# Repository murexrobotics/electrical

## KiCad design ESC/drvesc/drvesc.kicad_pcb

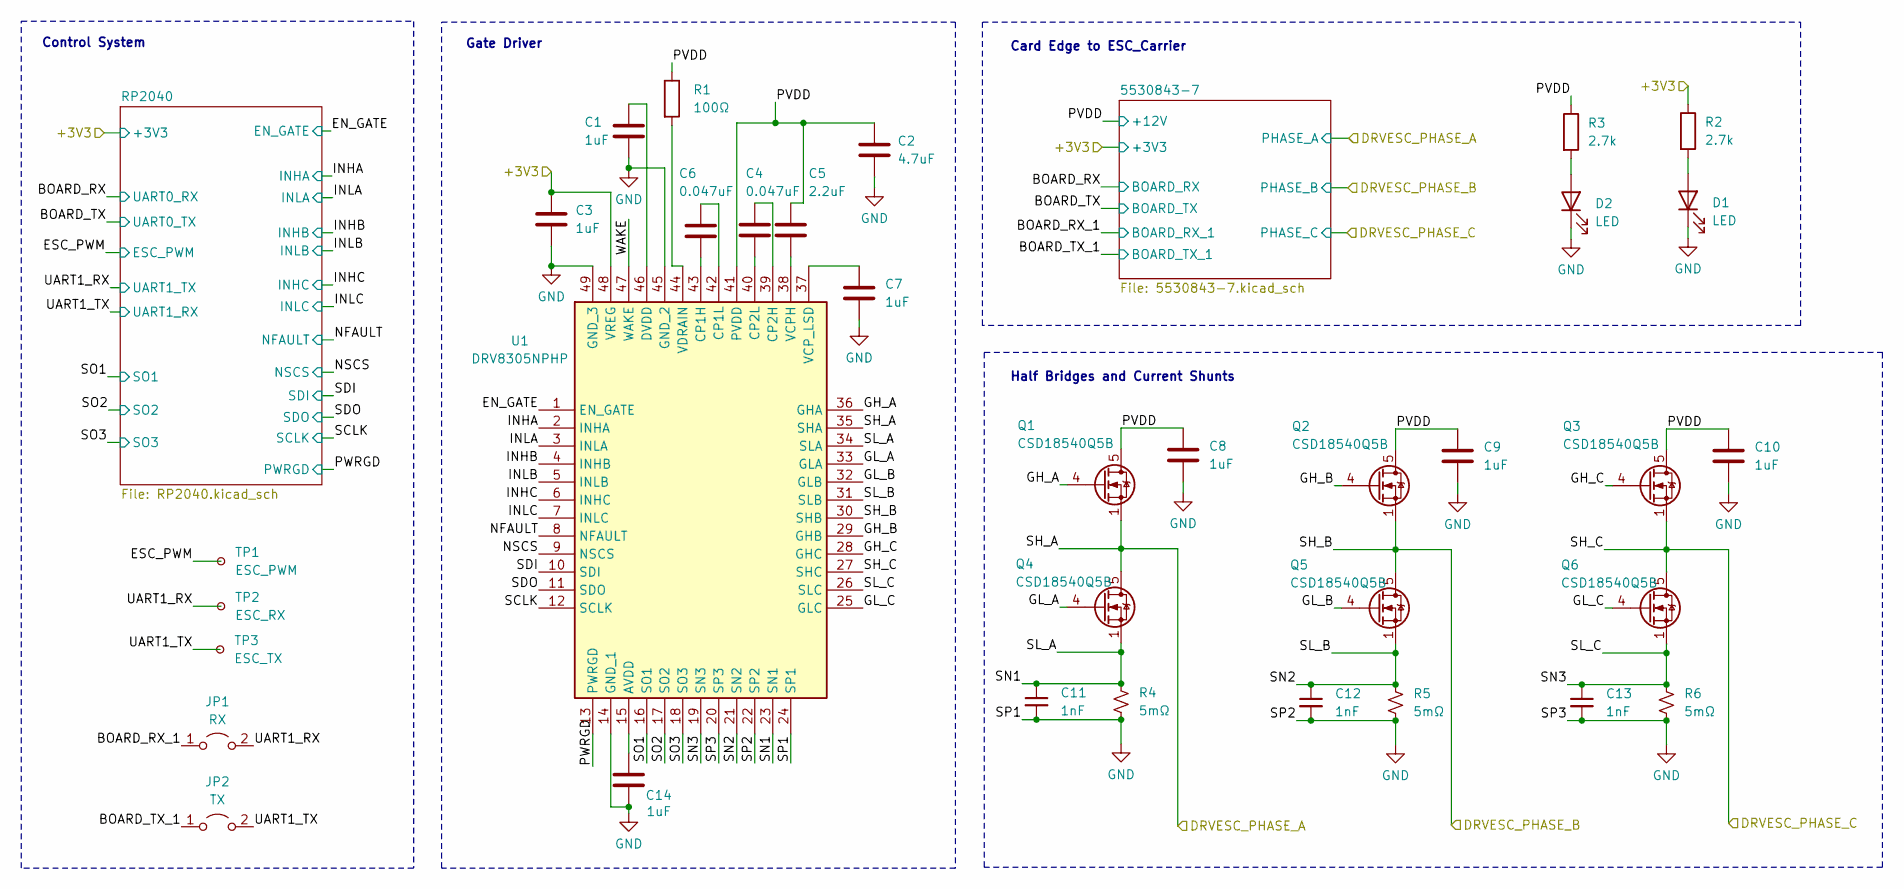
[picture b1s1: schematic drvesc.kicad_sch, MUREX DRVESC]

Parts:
C1, C3, C7, C8, C9, C10, C14: 1uF; C_0603_1608Metric
C2: 4.7uF; C_0603_1608Metric
C4, C6: 0.047uF; C_0603_1608Metric
C5: 2.2uF; C_0603_1608Metric
C11, C12, C13: 1nF; C_0603_1608Metric
D1, D2: LED; LED_0603_1608Metric
JP1: RX; SolderJumper-2_P1.3mm_Open_RoundedPad1.0x1.5mm
JP2: TX; SolderJumper-2_P1.3mm_Open_RoundedPad1.0x1.5mm
Q1, Q2, Q3, Q4, Q5, Q6: CSD18540Q5B; TDSON-8-1
R1: 100Ω; R_0603_1608Metric
R2, R3: 2.7k; R_0603_1608Metric
R4, R5, R6: 5mΩ; R_2512_6332Metric
TP1: ESC_PWM; PinHeader_1x01_P2.54mm_Vertical
TP2: ESC_RX; PinHeader_1x01_P2.54mm_Vertical
TP3: ESC_TX; PinHeader_1x01_P2.54mm_Vertical
U1: DRV8305NPHP; QFP50P900X900X120-49N; Manufacturer_Part_Number DRV8305NPHP; Mouser Part Number 595-DRV8305NPHP

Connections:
/+3V3: C3.1, R2.1, U1.48 (VREG); also elsewhere on the board
/BOARD_RX_1: JP1.1 (A); also elsewhere on the board
/BOARD_TX_1: JP2.1 (A); also elsewhere on the board
/EN_GATE: U1.1 (EN_GATE); also elsewhere on the board
/ESC_PWM: TP1.1; also elsewhere on the board
/GH_A: Q1.4 (G), U1.36 (GHA)
/GH_B: Q2.4 (G), U1.29 (GHB)
/GH_C: Q3.4 (G), U1.28 (GHC)
/GL_A: Q4.4 (G), U1.33 (GLA)
/GL_B: Q5.4 (G), U1.32 (GLB)
/GL_C: Q6.4 (G), U1.25 (GLC)
/INHA: U1.2 (INHA); also elsewhere on the board
/INHB: U1.4 (INHB); also elsewhere on the board
/INHC: U1.6 (INHC); also elsewhere on the board
/INLA: U1.3 (INLA); also elsewhere on the board
/INLB: U1.5 (INLB); also elsewhere on the board
/INLC: U1.7 (INLC); also elsewhere on the board
/NFAULT: U1.8 (NFAULT); also elsewhere on the board
/NSCS: U1.9 (NSCS); also elsewhere on the board
/PVDD: C2.1, C5.1, C8.1, C9.1, C10.1, Q1.5 (D), Q2.5 (D), Q3.5 (D), R1.1, R3.1, U1.41 (PVDD); also elsewhere on the board
/PWRGD: U1.13 (PWRGD); also elsewhere on the board
/SCLK: U1.12 (SCLK); also elsewhere on the board
/SDI: U1.10 (SDI); also elsewhere on the board
/SDO: U1.11 (SDO); also elsewhere on the board
/SH_A: Q1.1 (S), Q1.2 (S), Q1.3 (S), Q4.5 (D), U1.35 (SHA); also elsewhere on the board
/SH_B: Q2.1 (S), Q2.2 (S), Q2.3 (S), Q5.5 (D), U1.30 (SHB); also elsewhere on the board
/SH_C: Q3.1 (S), Q3.2 (S), Q3.3 (S), Q6.5 (D), U1.27 (SHC); also elsewhere on the board
/SL_A: C11.1, Q4.1 (S), Q4.2 (S), Q4.3 (S), R4.1, U1.23 (SN1), U1.34 (SLA)
/SL_B: C12.1, Q5.1 (S), Q5.2 (S), Q5.3 (S), R5.1, U1.21 (SN2), U1.31 (SLB)
/SL_C: C13.1, Q6.1 (S), Q6.2 (S), Q6.3 (S), R6.1, U1.19 (SN3), U1.26 (SLC)
/SO1: U1.16 (SO1); also elsewhere on the board
/SO2: U1.17 (SO2); also elsewhere on the board
/SO3: U1.18 (SO3); also elsewhere on the board
/UART1_RX: JP1.2 (B), TP2.1; also elsewhere on the board
/UART1_TX: JP2.2 (B), TP3.1; also elsewhere on the board
/WAKE: U1.47 (WAKE)
GND: C1.2, C2.2, C3.2, C7.2, C8.2, C9.2, C10.2, C11.2, C12.2, C13.2, C14.2, D1.1 (K), D2.1 (K), R4.2, R5.2, R6.2, U1.14 (GND_1), U1.20 (SP3), U1.22 (SP2), U1.24 (SP1), U1.45 (GND_2), U1.49 (GND_3); also elsewhere on the board
unnamed: D1.2 (A), R2.2
unnamed: D2.2 (A), R3.2
unnamed: C14.1, U1.15 (AVDD)
unnamed: C6.2, U1.43 (CP1H)
unnamed: C6.1, U1.42 (CP1L)
unnamed: C4.1, U1.39 (CP2H)
unnamed: C4.2, U1.40 (CP2L)
unnamed: C1.1, U1.46 (DVDD)
unnamed: C5.2, U1.38 (VCPH)
unnamed: C7.1, U1.37 (VCP_LSD)
unnamed: R1.2, U1.44 (VDRAIN)

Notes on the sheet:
Half Bridges and Current Shunts
Gate Driver
Control System
Card Edge to ESC_Carrier

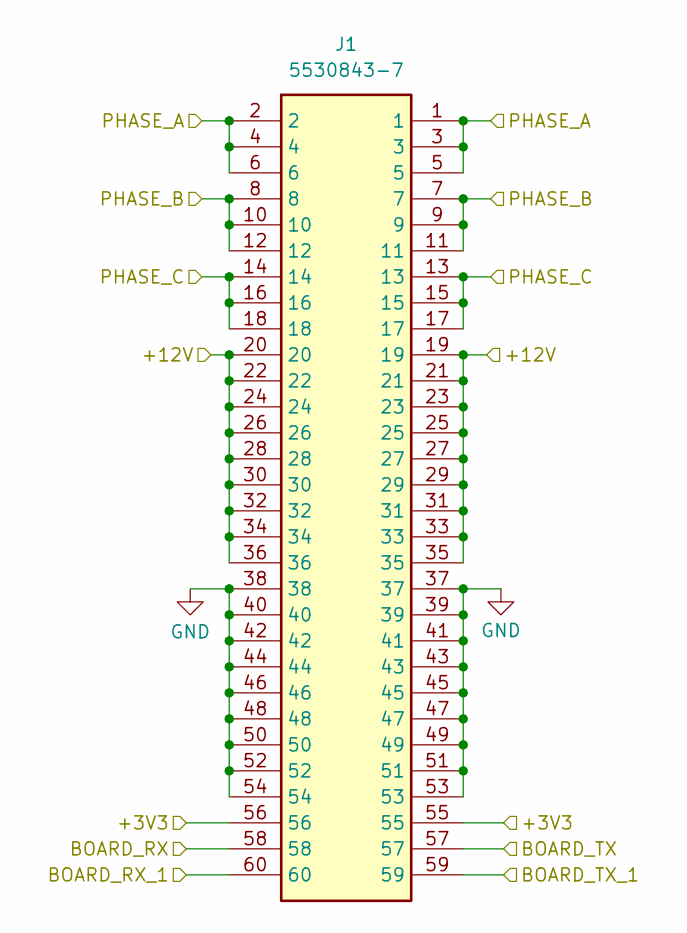
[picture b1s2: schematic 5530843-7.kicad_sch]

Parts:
J1: 5530843-7; TE_5530843-7_PCB_Edge; Manufacturer_Part_Number 5530843-7; Mouser Part Number 571-5530843-7

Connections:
/+3V3: J1.55, J1.56; also elsewhere on the board
/BOARD_RX: J1.58; also elsewhere on the board
/BOARD_RX_1: J1.60; also elsewhere on the board
/BOARD_TX: J1.57; also elsewhere on the board
/BOARD_TX_1: J1.59; also elsewhere on the board
/PVDD: J1.19, J1.20, J1.21, J1.22, J1.23, J1.24, J1.25, J1.26, J1.27, J1.28, J1.29, J1.30, J1.31, J1.32, J1.33, J1.34, J1.35, J1.36; also elsewhere on the board
/SH_A: J1.1, J1.2, J1.3, J1.4, J1.5, J1.6; also elsewhere on the board
/SH_B: J1.7, J1.8, J1.9, J1.10, J1.11, J1.12; also elsewhere on the board
/SH_C: J1.13, J1.14, J1.15, J1.16, J1.17, J1.18; also elsewhere on the board
GND: J1.37, J1.38, J1.39, J1.40, J1.41, J1.42, J1.43, J1.44, J1.45, J1.46, J1.47, J1.48, J1.49, J1.50, J1.51, J1.52, J1.53, J1.54; also elsewhere on the board

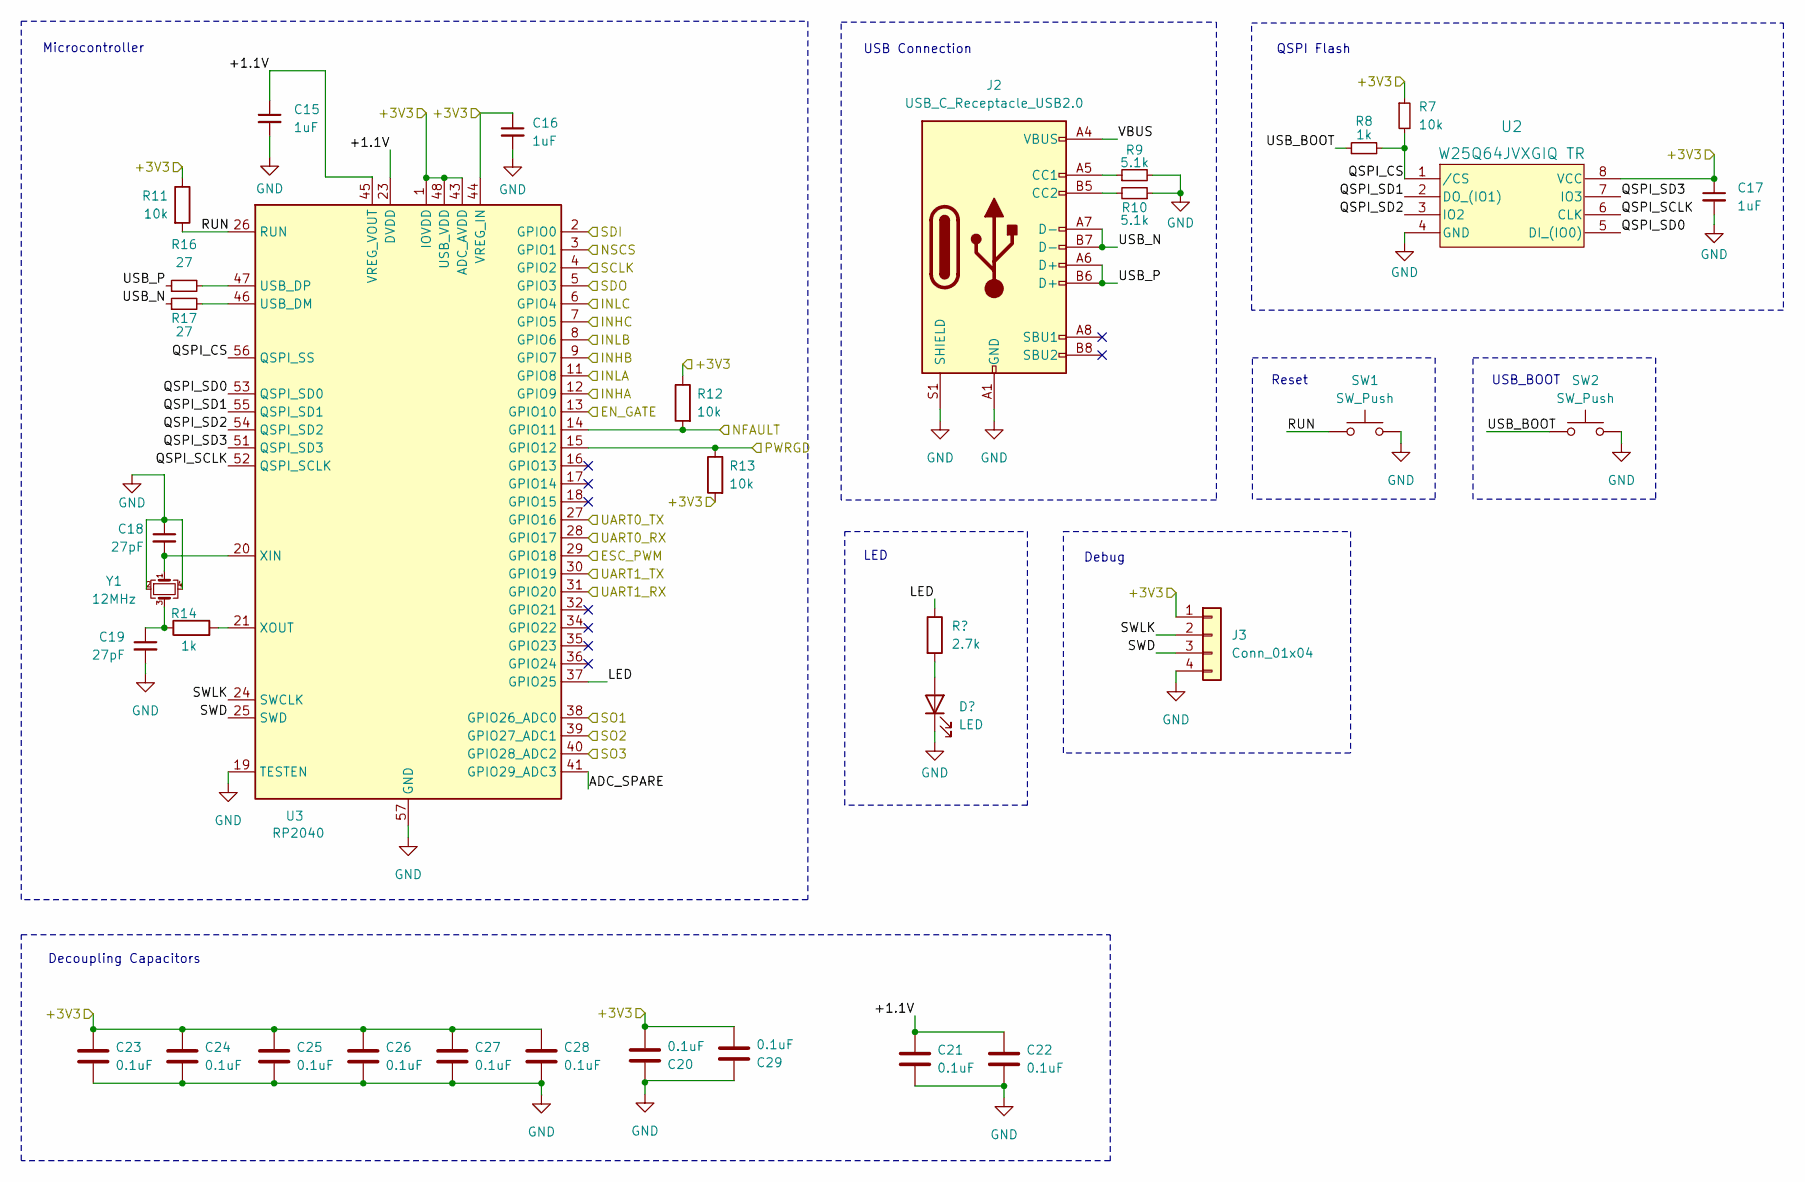
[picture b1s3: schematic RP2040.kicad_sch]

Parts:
C15, C16, C17: 1uF; C_0402_1005Metric
C18, C19: 27pF; C_0402_1005Metric
C20, C21, C22, C23, C24, C25, C26, C27, C28, C29: 0.1uF; C_0402_1005Metric
D3: LED; LED_0603_1608Metric
J2: USB_C_Receptacle_USB2.0; USB_C_Receptacle_HRO_TYPE-C-31-M-12
J3: Conn_01x04; PinHeader_1x04_P2.54mm_Horizontal
R7, R11, R12, R13: 10k; R_0603_1608Metric
R8: 1k; R_0603_1608Metric
R9, R10: 5.1k; R_0603_1608Metric
R14: 1k; R_0402_1005Metric
R15: 2.7k; R_0603_1608Metric
R16, R17: 27; R_0603_1608Metric
SW1, SW2: SW_Push; SW_PUSH_6mm_SLIM
U2: W25Q64JVXGIQ TR; DFN_XGIQ TR_WIN
U3: RP2040; QFN-56-1EP_7x7mm_P0.4mm_EP3.2x3.2mm
Y1: 12MHz; Crystal_SMD_2016-4Pin_2.0x1.6mm

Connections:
/+3V3: C16.1, C17.1, C20.2, C23.2, C24.1, C25.1, C26.1, C27.1, C28.1, C29.2, J3.1, R7.1, R11.1, R12.1, R13.2, U2.8 (VCC), U3.1 (IOVDD), U3.10 (IOVDD), U3.22 (IOVDD), U3.33 (IOVDD), U3.42 (IOVDD), U3.43 (ADC_AVDD), U3.44 (VREG_IN), U3.48 (USB_VDD), U3.49 (IOVDD); also elsewhere on the board
/BOARD_RX: U3.28 (GPIO17); also elsewhere on the board
/BOARD_TX: U3.27 (GPIO16); also elsewhere on the board
/EN_GATE: U3.13 (GPIO10); also elsewhere on the board
/ESC_PWM: U3.29 (GPIO18); also elsewhere on the board
/INHA: U3.12 (GPIO9); also elsewhere on the board
/INHB: U3.9 (GPIO7); also elsewhere on the board
/INHC: U3.7 (GPIO5); also elsewhere on the board
/INLA: U3.11 (GPIO8); also elsewhere on the board
/INLB: U3.8 (GPIO6); also elsewhere on the board
/INLC: U3.6 (GPIO4); also elsewhere on the board
/NFAULT: R12.2, U3.14 (GPIO11); also elsewhere on the board
/NSCS: U3.3 (GPIO1); also elsewhere on the board
/PWRGD: R13.1, U3.15 (GPIO12); also elsewhere on the board
/RP2040/+1.1V: C15.1, C21.1, C22.1, U3.23 (DVDD), U3.45 (VREG_VOUT), U3.50 (DVDD)
/RP2040/ADC_SPARE: U3.41 (GPIO29_ADC3)
/RP2040/LED: R15.1, U3.37 (GPIO25)
/RP2040/QSPI_CS: R7.2, R8.2, U2.1 (/CS), U3.56 (QSPI_SS)
/RP2040/QSPI_SCLK: U2.6 (CLK), U3.52 (QSPI_SCLK)
/RP2040/QSPI_SD0: U2.5 (DI_(IO0)), U3.53 (QSPI_SD0)
/RP2040/QSPI_SD1: U2.2 (DO_(IO1)), U3.55 (QSPI_SD1)
/RP2040/QSPI_SD2: U2.3 (IO2), U3.54 (QSPI_SD2)
/RP2040/QSPI_SD3: U2.7 (IO3), U3.51 (QSPI_SD3)
/RP2040/RUN: R11.2, SW1.1, U3.26 (RUN)
/RP2040/SWD: J3.3, U3.25 (SWD)
/RP2040/SWLK: J3.2, U3.24 (SWCLK)
/RP2040/USB_BOOT: R8.1, SW2.1
/RP2040/USB_N: J2.A7 (D-), J2.B7 (D-), R17.1
/RP2040/USB_P: J2.A6 (D+), J2.B6 (D+), R16.1
/RP2040/VBUS: J2.A4 (VBUS), J2.A9 (VBUS), J2.B4 (VBUS), J2.B9 (VBUS)
/SCLK: U3.4 (GPIO2); also elsewhere on the board
/SDI: U3.2 (GPIO0); also elsewhere on the board
/SDO: U3.5 (GPIO3); also elsewhere on the board
/SO1: U3.38 (GPIO26_ADC0); also elsewhere on the board
/SO2: U3.39 (GPIO27_ADC1); also elsewhere on the board
/SO3: U3.40 (GPIO28_ADC2); also elsewhere on the board
/UART1_RX: U3.30 (GPIO19); also elsewhere on the board
/UART1_TX: U3.31 (GPIO20); also elsewhere on the board
GND: C15.2, C16.2, C17.2, C18.1, C19.2, C20.1, C21.2, C22.2, C23.1, C24.2, C25.2, C26.2, C27.2, C28.2, C29.1, D3.1 (K), J2.A1 (GND), J2.A12 (GND), J2.B1 (GND), J2.B12 (GND), J2.S1 (SHIELD), J3.4, R9.2, R10.1, SW1.2, SW2.2, U2.4 (GND), U3.19 (TESTEN), U3.57 (GND), Y1.2, Y1.4; also elsewhere on the board
unnamed: C19.1, R14.1, Y1.3
unnamed: D3.2 (A), R15.2
unnamed: J2.A5 (CC1), R9.1
unnamed: J2.B5 (CC2), R10.2
unnamed: R17.2, U3.46 (USB_DM)
unnamed: R16.2, U3.47 (USB_DP)
unnamed: C18.2, U3.20 (XIN), Y1.1
unnamed: R14.2, U3.21 (XOUT)

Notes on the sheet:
Microcontroller
Debug
USB Connection
QSPI Flash
Decoupling Capacitors
LED
USB_BOOT
Reset

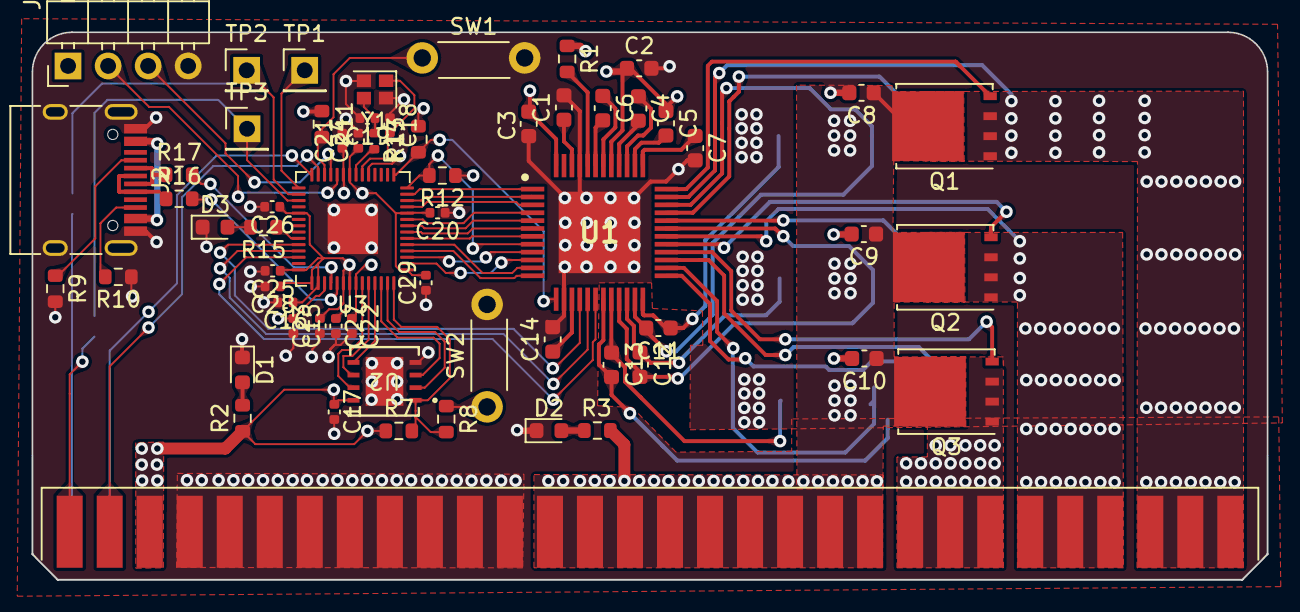
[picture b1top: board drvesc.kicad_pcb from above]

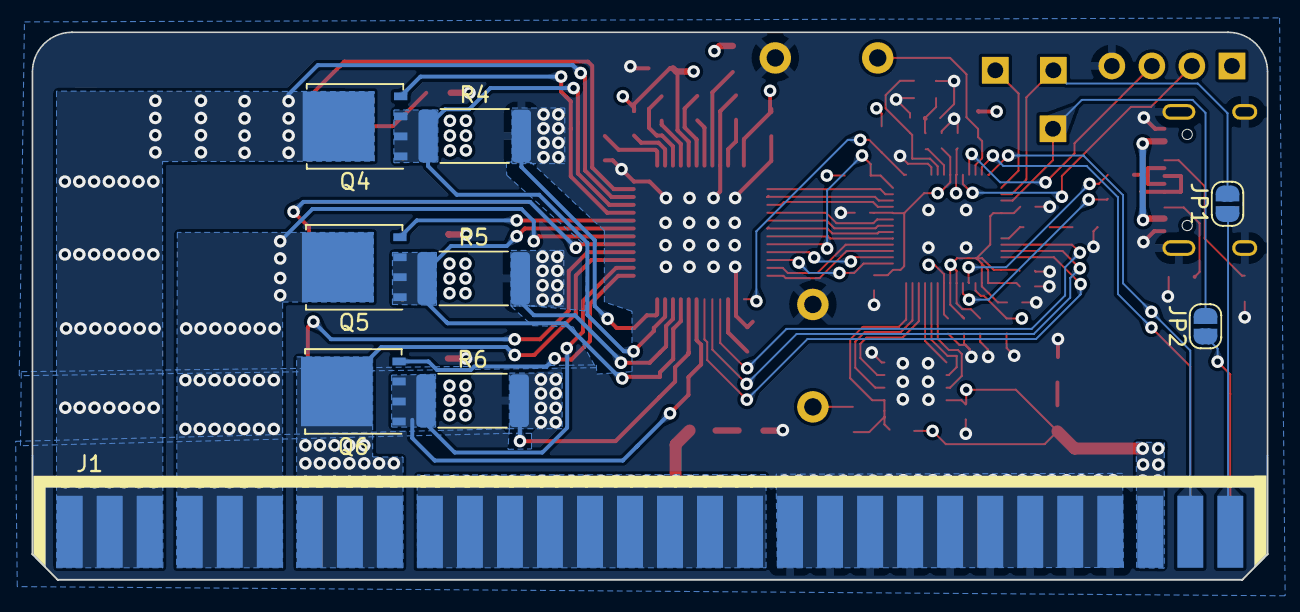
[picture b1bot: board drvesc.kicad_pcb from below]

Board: 4 copper layers, 78.4 x 34.7 mm, 69 parts (9 on the bottom side), 72 nets.

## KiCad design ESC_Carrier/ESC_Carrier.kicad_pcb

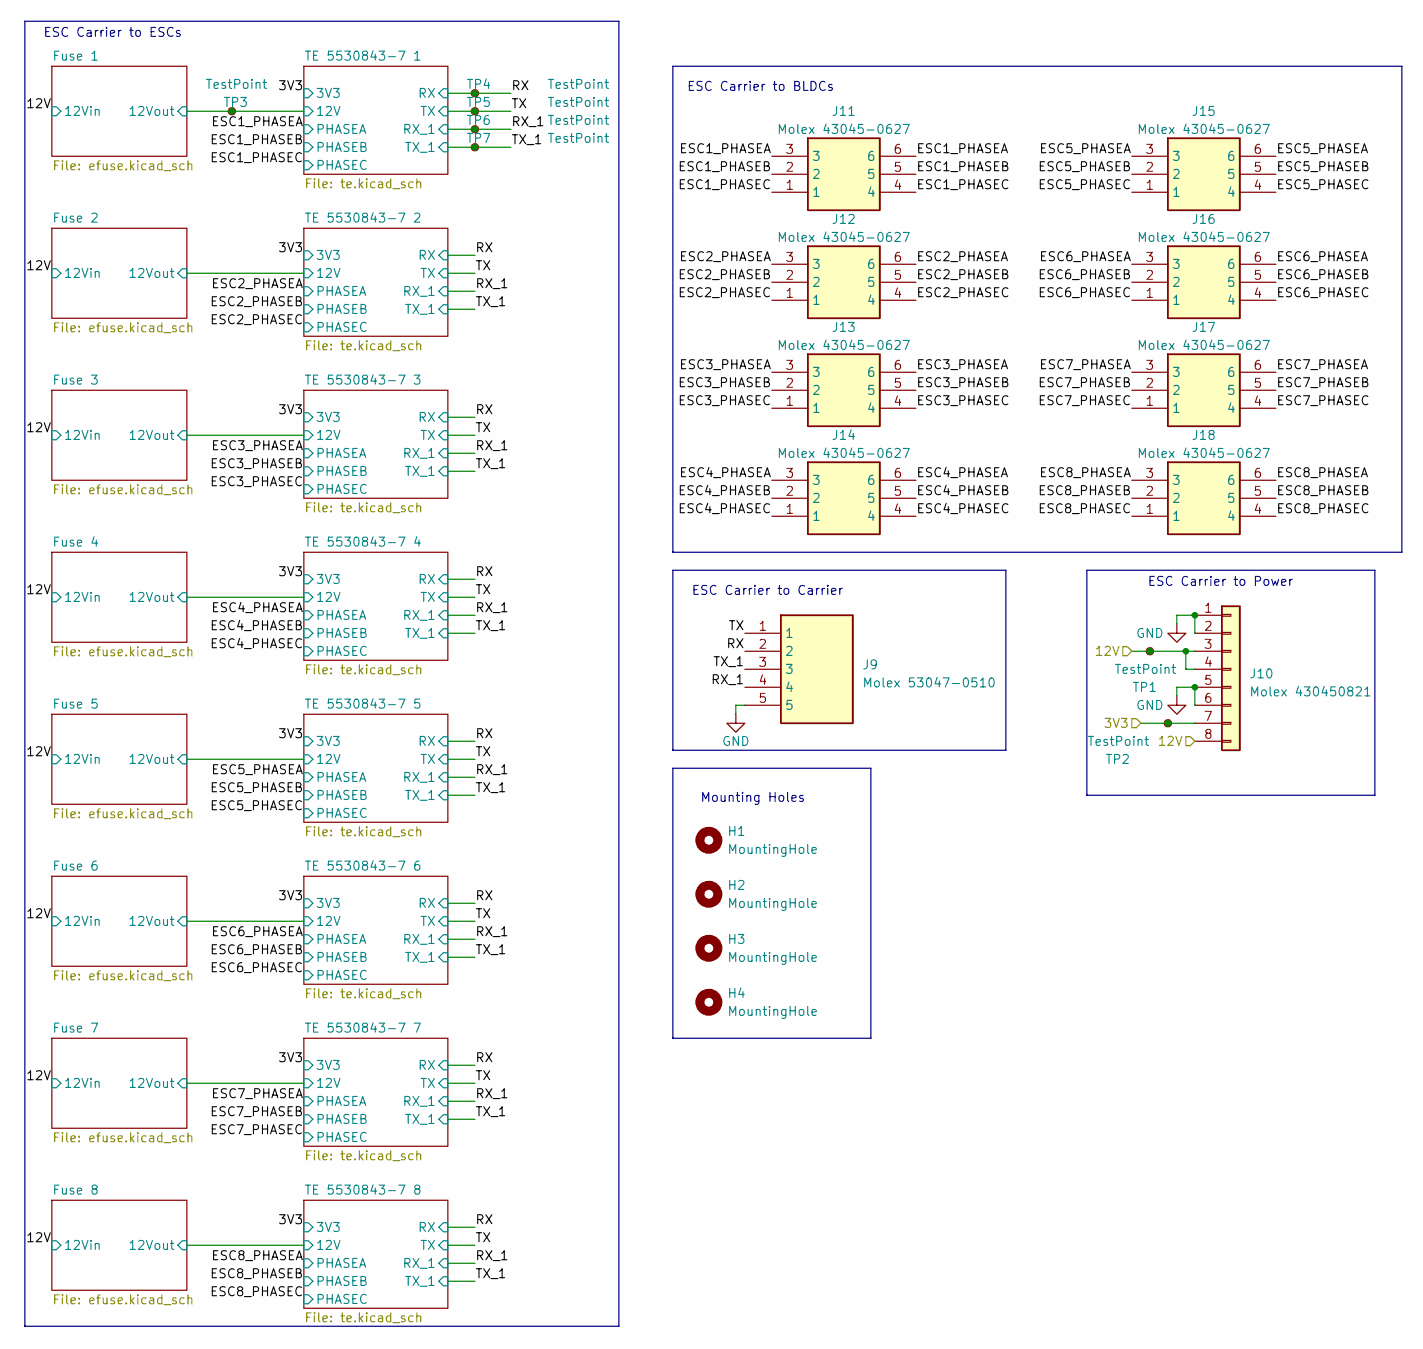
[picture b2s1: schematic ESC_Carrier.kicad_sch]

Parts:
H1, H2, H3, H4: MountingHole; MountingHole_2.7mm_M2.5
J9: Molex 53047-0510; SHDR5W27P0X125_1X5_800X320X440P; Manufacturer_Part_Number 53047-0510; Mouser Part Number 538-53047-0510
J10: Molex 430450821; CON_430450821_MOL
J11, J12, J13, J14, J15, J16, J17, J18: Molex 43045-0627; 43045-06YY_272829; Manufacturer_Part_Number 43045-0627; Mouser Part Number 538-43045-0627
TP1, TP2, TP3, TP4, TP5, TP6, TP7: TestPoint; TestPoint_Pad_D2.0mm

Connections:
/3V3: J10.7, TP2.1; also elsewhere on the board
/12V: J10.3, J10.4, J10.8, TP1.1; also elsewhere on the board
/ESC1_PHASEA: J11.3, J11.6; also elsewhere on the board
/ESC1_PHASEB: J11.2, J11.5; also elsewhere on the board
/ESC1_PHASEC: J11.1, J11.4; also elsewhere on the board
/ESC2_PHASEA: J12.3, J12.6; also elsewhere on the board
/ESC2_PHASEB: J12.2, J12.5; also elsewhere on the board
/ESC2_PHASEC: J12.1, J12.4; also elsewhere on the board
/ESC3_PHASEA: J13.3, J13.6; also elsewhere on the board
/ESC3_PHASEB: J13.2, J13.5; also elsewhere on the board
/ESC3_PHASEC: J13.1, J13.4; also elsewhere on the board
/ESC4_PHASEA: J14.3, J14.6; also elsewhere on the board
/ESC4_PHASEB: J14.2, J14.5; also elsewhere on the board
/ESC4_PHASEC: J14.1, J14.4; also elsewhere on the board
/ESC5_PHASEA: J15.3, J15.6; also elsewhere on the board
/ESC5_PHASEB: J15.2, J15.5; also elsewhere on the board
/ESC5_PHASEC: J15.1, J15.4; also elsewhere on the board
/ESC6_PHASEA: J16.3, J16.6; also elsewhere on the board
/ESC6_PHASEB: J16.2, J16.5; also elsewhere on the board
/ESC6_PHASEC: J16.1, J16.4; also elsewhere on the board
/ESC7_PHASEA: J17.3, J17.6; also elsewhere on the board
/ESC7_PHASEB: J17.2, J17.5; also elsewhere on the board
/ESC7_PHASEC: J17.1, J17.4; also elsewhere on the board
/ESC8_PHASEA: J18.3, J18.6; also elsewhere on the board
/ESC8_PHASEB: J18.2, J18.5; also elsewhere on the board
/ESC8_PHASEC: J18.1, J18.4; also elsewhere on the board
/Fuse 1/12Vout: TP3.1; also elsewhere on the board
/RX: J9.2, TP4.1; also elsewhere on the board
/RX_1: J9.4, TP6.1; also elsewhere on the board
/TX: J9.1, TP5.1; also elsewhere on the board
/TX_1: J9.3, TP7.1; also elsewhere on the board
GND: J9.5, J10.1, J10.2, J10.5, J10.6; also elsewhere on the board

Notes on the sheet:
ESC Carrier to Carrier
ESC Carrier to ESCs
ESC Carrier to BLDCs
Mounting Holes
ESC Carrier to Power

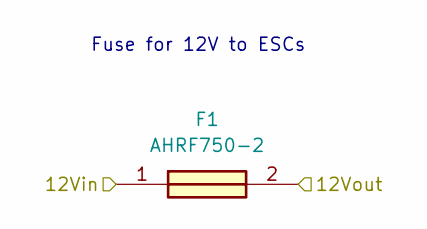
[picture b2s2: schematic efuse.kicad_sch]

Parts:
F1: AHRF750-2; AHRF7502; Manufacturer_Part_Number AHRF750-2

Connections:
/12V: F1.1; also elsewhere on the board
/Fuse 1/12Vout: F1.2; also elsewhere on the board

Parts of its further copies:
F2, F3, F4, F5, F6, F7, F8: AHRF750-2; AHRF7502; Manufacturer_Part_Number AHRF750-2

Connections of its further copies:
/12V: F2.1, F3.1, F4.1, F5.1, F6.1, F7.1, F8.1; also elsewhere on the board
/Fuse 2/12Vout: F2.2; also elsewhere on the board
/Fuse 3/12Vout: F3.2; also elsewhere on the board
/Fuse 4/12Vout: F4.2; also elsewhere on the board
/Fuse 5/12Vout: F5.2; also elsewhere on the board
/Fuse 6/12Vout: F6.2; also elsewhere on the board
/Fuse 7/12Vout: F7.2; also elsewhere on the board
/Fuse 8/12Vout: F8.2; also elsewhere on the board

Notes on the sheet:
Fuse for 12V to ESCs

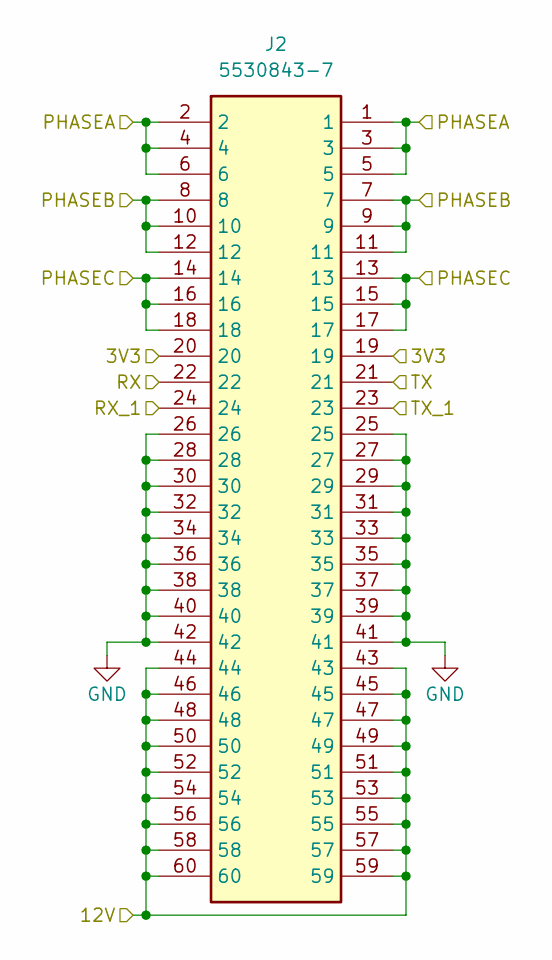
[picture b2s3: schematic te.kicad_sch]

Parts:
J2: 5530843-7; 55308437; Manufacturer_Part_Number 5530843-7; Mouser Part Number 571-5530843-7

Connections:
/3V3: J2.19, J2.20; also elsewhere on the board
/ESC2_PHASEA: J2.1, J2.2, J2.3, J2.4, J2.5, J2.6; also elsewhere on the board
/ESC2_PHASEB: J2.7, J2.8, J2.9, J2.10, J2.11, J2.12; also elsewhere on the board
/ESC2_PHASEC: J2.13, J2.14, J2.15, J2.16, J2.17, J2.18; also elsewhere on the board
/Fuse 2/12Vout: J2.43, J2.44, J2.45, J2.46, J2.47, J2.48, J2.49, J2.50, J2.51, J2.52, J2.53, J2.54, J2.55, J2.56, J2.57, J2.58, J2.59, J2.60; also elsewhere on the board
/RX: J2.22; also elsewhere on the board
/RX_1: J2.24; also elsewhere on the board
/TX: J2.21; also elsewhere on the board
/TX_1: J2.23; also elsewhere on the board
GND: J2.25, J2.26, J2.27, J2.28, J2.29, J2.30, J2.31, J2.32, J2.33, J2.34, J2.35, J2.36, J2.37, J2.38, J2.39, J2.40, J2.41, J2.42; also elsewhere on the board

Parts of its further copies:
J1, J3, J4, J5, J6, J7, J8: 5530843-7; 55308437; Manufacturer_Part_Number 5530843-7; Mouser Part Number 571-5530843-7

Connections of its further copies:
/3V3: J1.19, J1.20, J3.19, J3.20, J4.19, J4.20, J5.19, J5.20, J6.19, J6.20, J7.19, J7.20, J8.19, J8.20; also elsewhere on the board
/ESC1_PHASEA: J1.1, J1.2, J1.3, J1.4, J1.5, J1.6; also elsewhere on the board
/ESC1_PHASEB: J1.7, J1.8, J1.9, J1.10, J1.11, J1.12; also elsewhere on the board
/ESC1_PHASEC: J1.13, J1.14, J1.15, J1.16, J1.17, J1.18; also elsewhere on the board
/ESC3_PHASEA: J3.1, J3.2, J3.3, J3.4, J3.5, J3.6; also elsewhere on the board
/ESC3_PHASEB: J3.7, J3.8, J3.9, J3.10, J3.11, J3.12; also elsewhere on the board
/ESC3_PHASEC: J3.13, J3.14, J3.15, J3.16, J3.17, J3.18; also elsewhere on the board
/ESC4_PHASEA: J4.1, J4.2, J4.3, J4.4, J4.5, J4.6; also elsewhere on the board
/ESC4_PHASEB: J4.7, J4.8, J4.9, J4.10, J4.11, J4.12; also elsewhere on the board
/ESC4_PHASEC: J4.13, J4.14, J4.15, J4.16, J4.17, J4.18; also elsewhere on the board
/ESC5_PHASEA: J5.1, J5.2, J5.3, J5.4, J5.5, J5.6; also elsewhere on the board
/ESC5_PHASEB: J5.7, J5.8, J5.9, J5.10, J5.11, J5.12; also elsewhere on the board
/ESC5_PHASEC: J5.13, J5.14, J5.15, J5.16, J5.17, J5.18; also elsewhere on the board
/ESC6_PHASEA: J6.1, J6.2, J6.3, J6.4, J6.5, J6.6; also elsewhere on the board
/ESC6_PHASEB: J6.7, J6.8, J6.9, J6.10, J6.11, J6.12; also elsewhere on the board
/ESC6_PHASEC: J6.13, J6.14, J6.15, J6.16, J6.17, J6.18; also elsewhere on the board
/ESC7_PHASEA: J7.1, J7.2, J7.3, J7.4, J7.5, J7.6; also elsewhere on the board
/ESC7_PHASEB: J7.7, J7.8, J7.9, J7.10, J7.11, J7.12; also elsewhere on the board
/ESC7_PHASEC: J7.13, J7.14, J7.15, J7.16, J7.17, J7.18; also elsewhere on the board
/ESC8_PHASEA: J8.1, J8.2, J8.3, J8.4, J8.5, J8.6; also elsewhere on the board
/ESC8_PHASEB: J8.7, J8.8, J8.9, J8.10, J8.11, J8.12; also elsewhere on the board
/ESC8_PHASEC: J8.13, J8.14, J8.15, J8.16, J8.17, J8.18; also elsewhere on the board
/Fuse 1/12Vout: J1.43, J1.44, J1.45, J1.46, J1.47, J1.48, J1.49, J1.50, J1.51, J1.52, J1.53, J1.54, J1.55, J1.56, J1.57, J1.58, J1.59, J1.60; also elsewhere on the board
/Fuse 3/12Vout: J3.43, J3.44, J3.45, J3.46, J3.47, J3.48, J3.49, J3.50, J3.51, J3.52, J3.53, J3.54, J3.55, J3.56, J3.57, J3.58, J3.59, J3.60; also elsewhere on the board
/Fuse 4/12Vout: J4.43, J4.44, J4.45, J4.46, J4.47, J4.48, J4.49, J4.50, J4.51, J4.52, J4.53, J4.54, J4.55, J4.56, J4.57, J4.58, J4.59, J4.60; also elsewhere on the board
/Fuse 5/12Vout: J5.43, J5.44, J5.45, J5.46, J5.47, J5.48, J5.49, J5.50, J5.51, J5.52, J5.53, J5.54, J5.55, J5.56, J5.57, J5.58, J5.59, J5.60; also elsewhere on the board
/Fuse 6/12Vout: J6.43, J6.44, J6.45, J6.46, J6.47, J6.48, J6.49, J6.50, J6.51, J6.52, J6.53, J6.54, J6.55, J6.56, J6.57, J6.58, J6.59, J6.60; also elsewhere on the board
/Fuse 7/12Vout: J7.43, J7.44, J7.45, J7.46, J7.47, J7.48, J7.49, J7.50, J7.51, J7.52, J7.53, J7.54, J7.55, J7.56, J7.57, J7.58, J7.59, J7.60; also elsewhere on the board
/Fuse 8/12Vout: J8.43, J8.44, J8.45, J8.46, J8.47, J8.48, J8.49, J8.50, J8.51, J8.52, J8.53, J8.54, J8.55, J8.56, J8.57, J8.58, J8.59, J8.60; also elsewhere on the board
/RX: J1.22, J3.22, J4.22, J5.22, J6.22, J7.22, J8.22; also elsewhere on the board
/RX_1: J1.24, J3.24, J4.24, J5.24, J6.24, J7.24, J8.24; also elsewhere on the board
/TX: J1.21, J3.21, J4.21, J5.21, J6.21, J7.21, J8.21; also elsewhere on the board
/TX_1: J1.23, J3.23, J4.23, J5.23, J6.23, J7.23, J8.23; also elsewhere on the board
GND: J1.25, J1.26, J1.27, J1.28, J1.29, J1.30, J1.31, J1.32, J1.33, J1.34, J1.35, J1.36, J1.37, J1.38, J1.39, J1.40, J1.41, J1.42, J3.25, J3.26, J3.27, J3.28, J3.29, J3.30, J3.31, J3.32, J3.33, J3.34, J3.35, J3.36, J3.37, J3.38, J3.39, J3.40, J3.41, J3.42, J4.25, J4.26, J4.27, J4.28, J4.29, J4.30, J4.31, J4.32, J4.33, J4.34, J4.35, J4.36, J4.37, J4.38, J4.39, J4.40, J4.41, J4.42, J5.25, J5.26, J5.27, J5.28, J5.29, J5.30, J5.31, J5.32, J5.33, J5.34, J5.35, J5.36, J5.37, J5.38, J5.39, J5.40, J5.41, J5.42, J6.25, J6.26, J6.27, J6.28, J6.29, J6.30, J6.31, J6.32, J6.33, J6.34, J6.35, J6.36, J6.37, J6.38, J6.39, J6.40, J6.41, J6.42, J7.25, J7.26, J7.27, J7.28, J7.29, J7.30, J7.31, J7.32, J7.33, J7.34, J7.35, J7.36, J7.37, J7.38, J7.39, J7.40, J7.41, J7.42, J8.25, J8.26, J8.27, J8.28, J8.29, J8.30, J8.31, J8.32, J8.33, J8.34, J8.35, J8.36, J8.37, J8.38, J8.39, J8.40, J8.41, J8.42; also elsewhere on the board

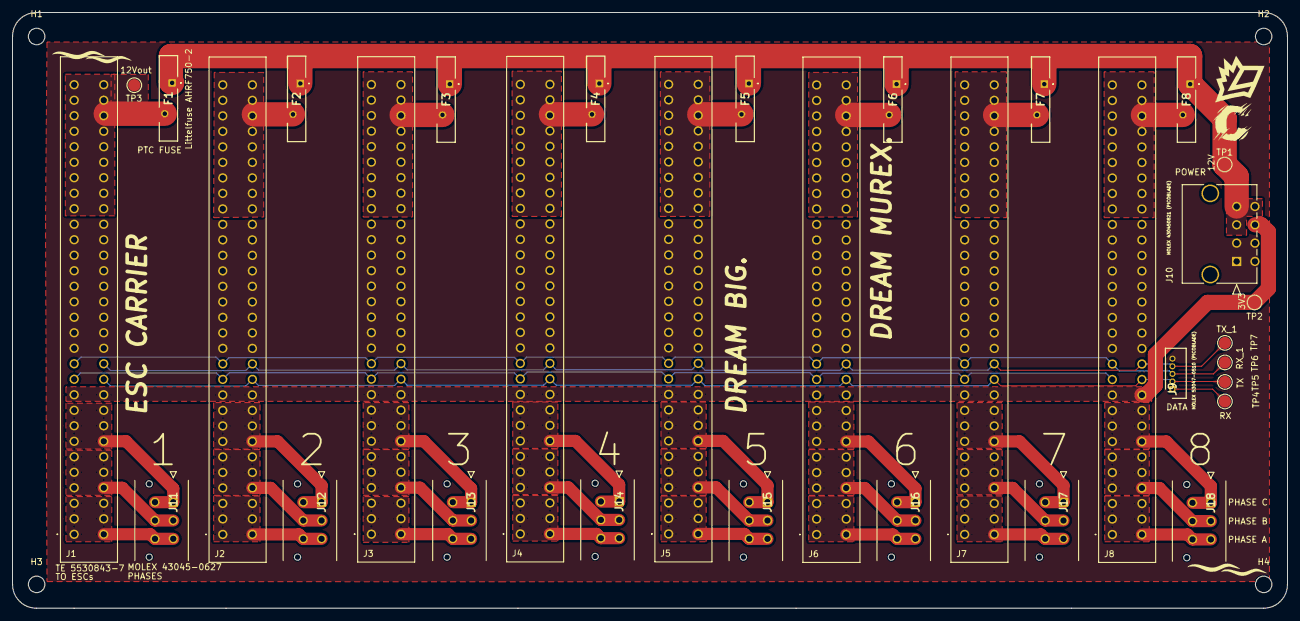
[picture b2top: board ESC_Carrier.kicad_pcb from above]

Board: 2 copper layers, 208.9 x 97.6 mm, 37 parts (0 on the bottom side), 39 nets.

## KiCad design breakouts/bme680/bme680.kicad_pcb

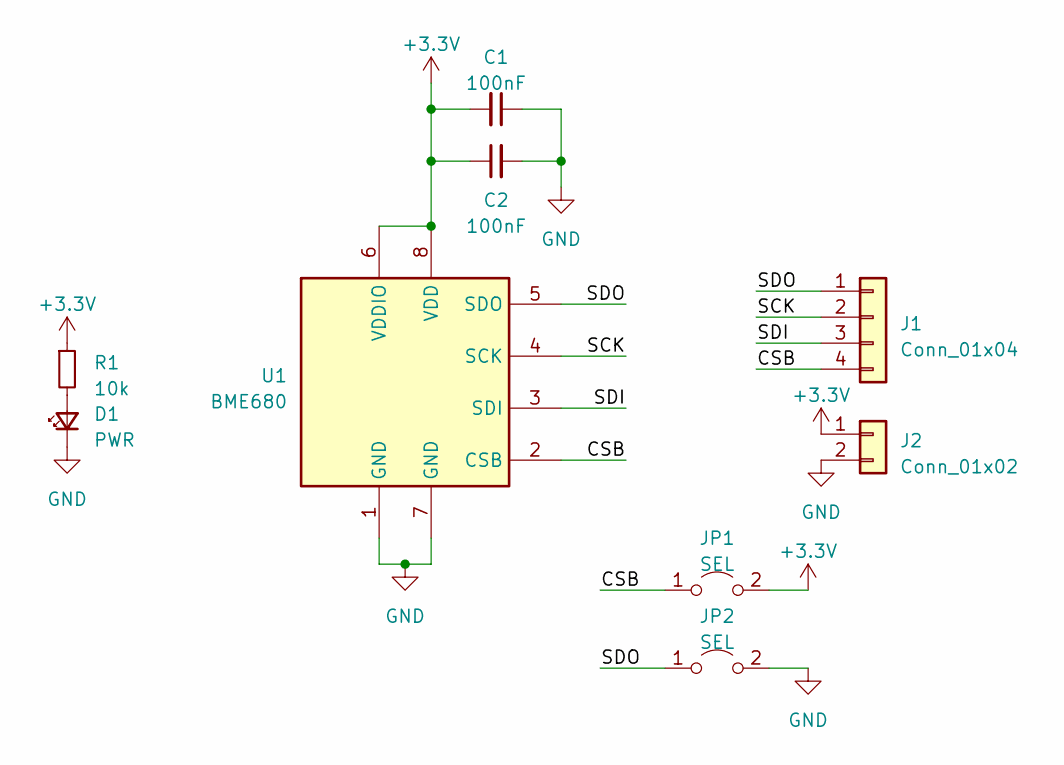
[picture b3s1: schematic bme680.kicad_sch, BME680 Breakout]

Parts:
C1, C2: 100nF; C_0603_1608Metric
D1: PWR; LED_0603_1608Metric
J1: Conn_01x04; PinHeader_1x04_P2.54mm_Vertical
J2: Conn_01x02; PinHeader_1x02_P2.54mm_Vertical
JP1, JP2: SEL; SolderJumper-2_P1.3mm_Open_Pad1.0x1.5mm
R1: 10k; R_0603_1608Metric
U1: BME680; Bosch_LGA-8_3x3mm_P0.8mm_ClockwisePinNumbering

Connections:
+3.3V: C1.2, C2.1, J2.1, JP1.2 (B), R1.1, U1.6 (VDDIO), U1.8 (VDD)
/CSB: J1.4, JP1.1 (A), U1.2 (CSB)
/SCK: J1.2, U1.4 (SCK)
/SDI: J1.3, U1.3 (SDI)
/SDO: J1.1, JP2.1 (A), U1.5 (SDO)
GND: C1.1, C2.2, D1.1 (K), J2.2, JP2.2 (B), U1.1 (GND), U1.7 (GND)
unnamed: D1.2 (A), R1.2

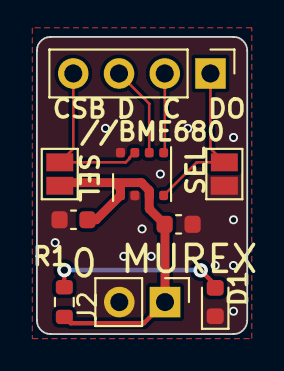
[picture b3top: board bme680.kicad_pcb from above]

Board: 2 copper layers, 11.7 x 16.5 mm, 9 parts (0 on the bottom side), 7 nets.

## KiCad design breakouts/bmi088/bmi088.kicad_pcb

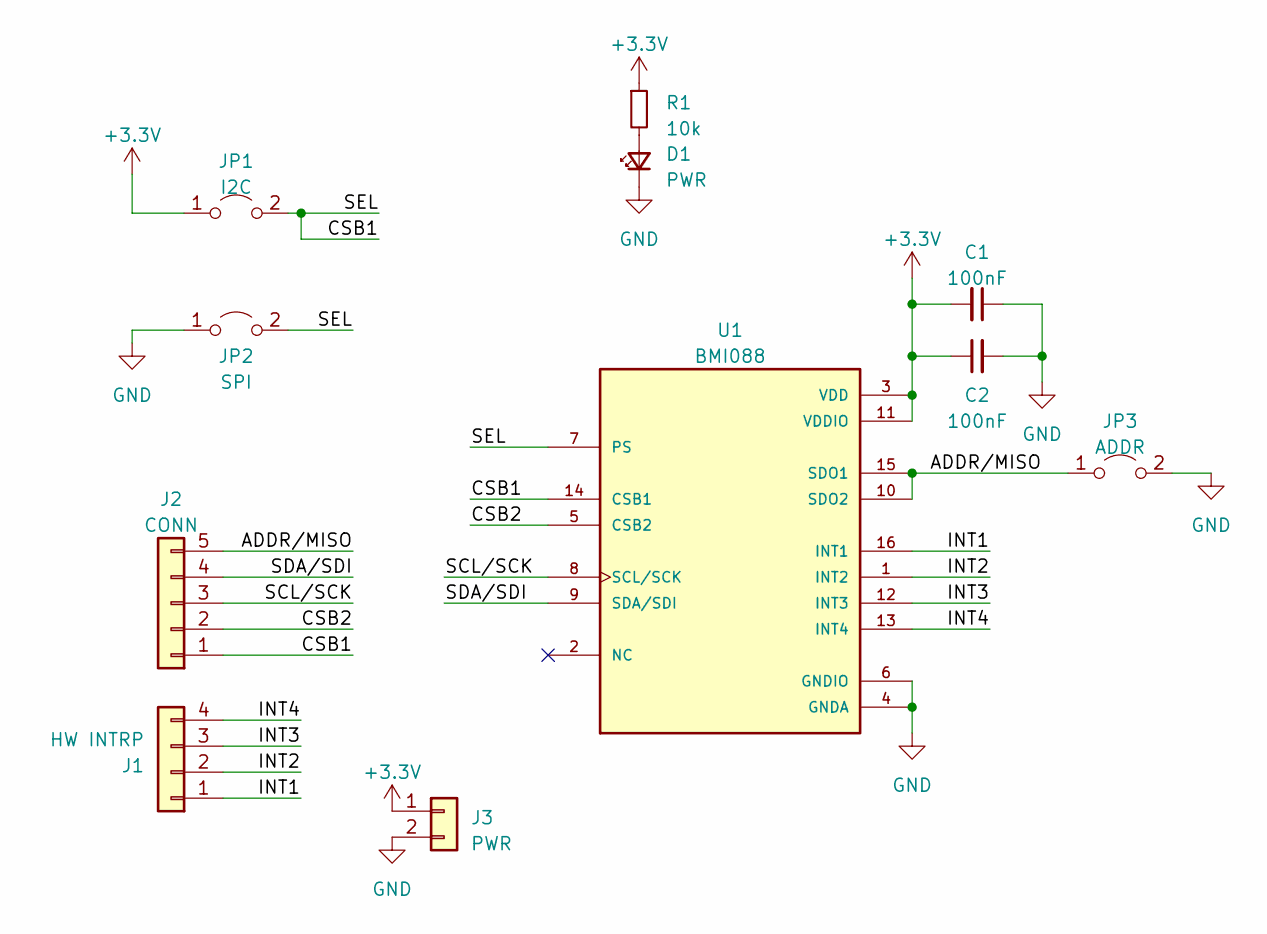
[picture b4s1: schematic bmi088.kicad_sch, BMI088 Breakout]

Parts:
C1, C2: 100nF; C_0603_1608Metric
D1: PWR; LED_0603_1608Metric
J1: HW INTRP; PinHeader_1x04_P2.54mm_Vertical
J2: CONN; PinHeader_1x05_P2.54mm_Vertical
J3: PWR; PinHeader_1x02_P2.54mm_Vertical
JP1: I2C; SolderJumper-2_P1.3mm_Open_Pad1.0x1.5mm
JP2: SPI; SolderJumper-2_P1.3mm_Open_Pad1.0x1.5mm
JP3: ADDR; SolderJumper-2_P1.3mm_Open_Pad1.0x1.5mm
R1: 10k; R_0603_1608Metric
U1: BMI088; PQFN50P450X300X100-16N

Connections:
+3.3V: C1.2, C2.1, J3.1, JP1.1 (A), R1.1, U1.3 (VDD), U1.11 (VDDIO)
/ADDR/MISO: J2.5, JP3.1 (A), U1.10 (SDO2), U1.15 (SDO1)
/CSB1: J2.1, JP1.2 (B), JP2.2 (B), U1.7 (PS), U1.14 (CSB1)
/CSB2: J2.2, U1.5 (CSB2)
/INT1: J1.1, U1.16 (INT1)
/INT2: J1.2, U1.1 (INT2)
/INT3: J1.3, U1.12 (INT3)
/INT4: J1.4, U1.13 (INT4)
/SCL/SCK: J2.3, U1.8 (SCL/SCK)
/SDA/SDI: J2.4, U1.9 (SDA/SDI)
GND: C1.1, C2.2, D1.1 (K), J3.2, JP2.1 (A), JP3.2 (B), U1.4 (GNDA), U1.6 (GNDIO)
unnamed: D1.2 (A), R1.2

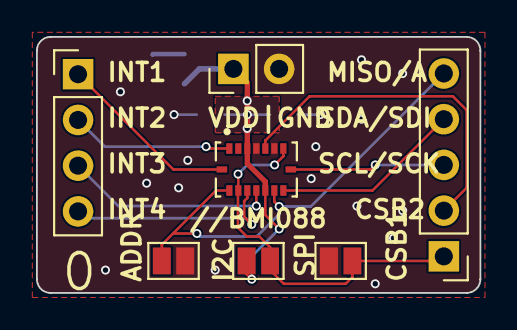
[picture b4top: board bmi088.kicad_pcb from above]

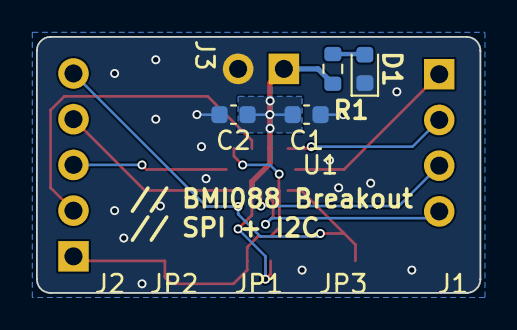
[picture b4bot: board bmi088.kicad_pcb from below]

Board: 2 copper layers, 24.6 x 14.2 mm, 11 parts (4 on the bottom side), 12 nets.
